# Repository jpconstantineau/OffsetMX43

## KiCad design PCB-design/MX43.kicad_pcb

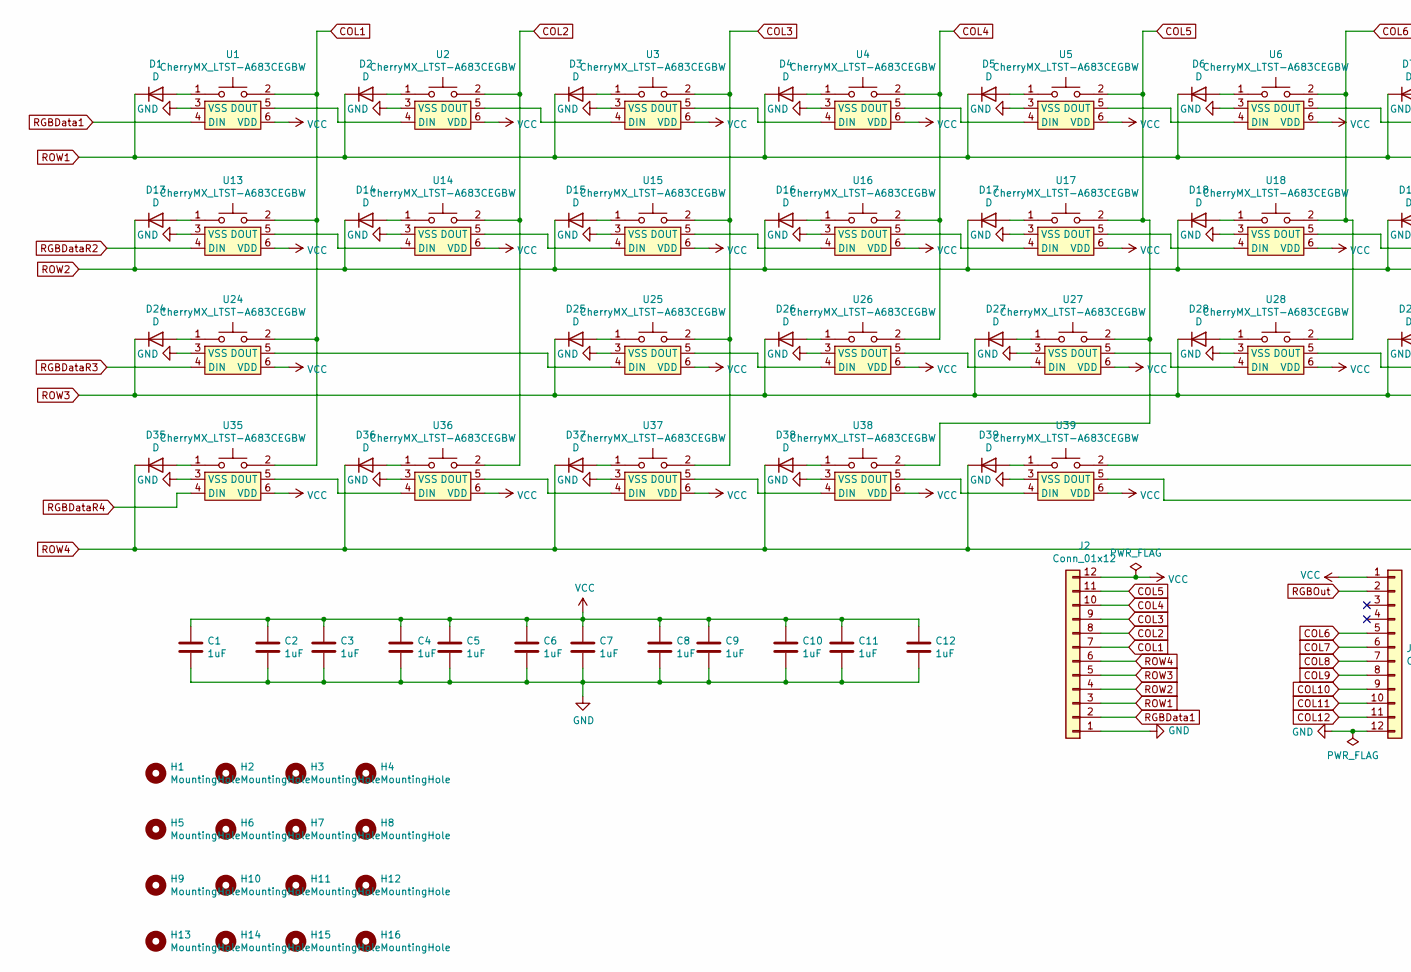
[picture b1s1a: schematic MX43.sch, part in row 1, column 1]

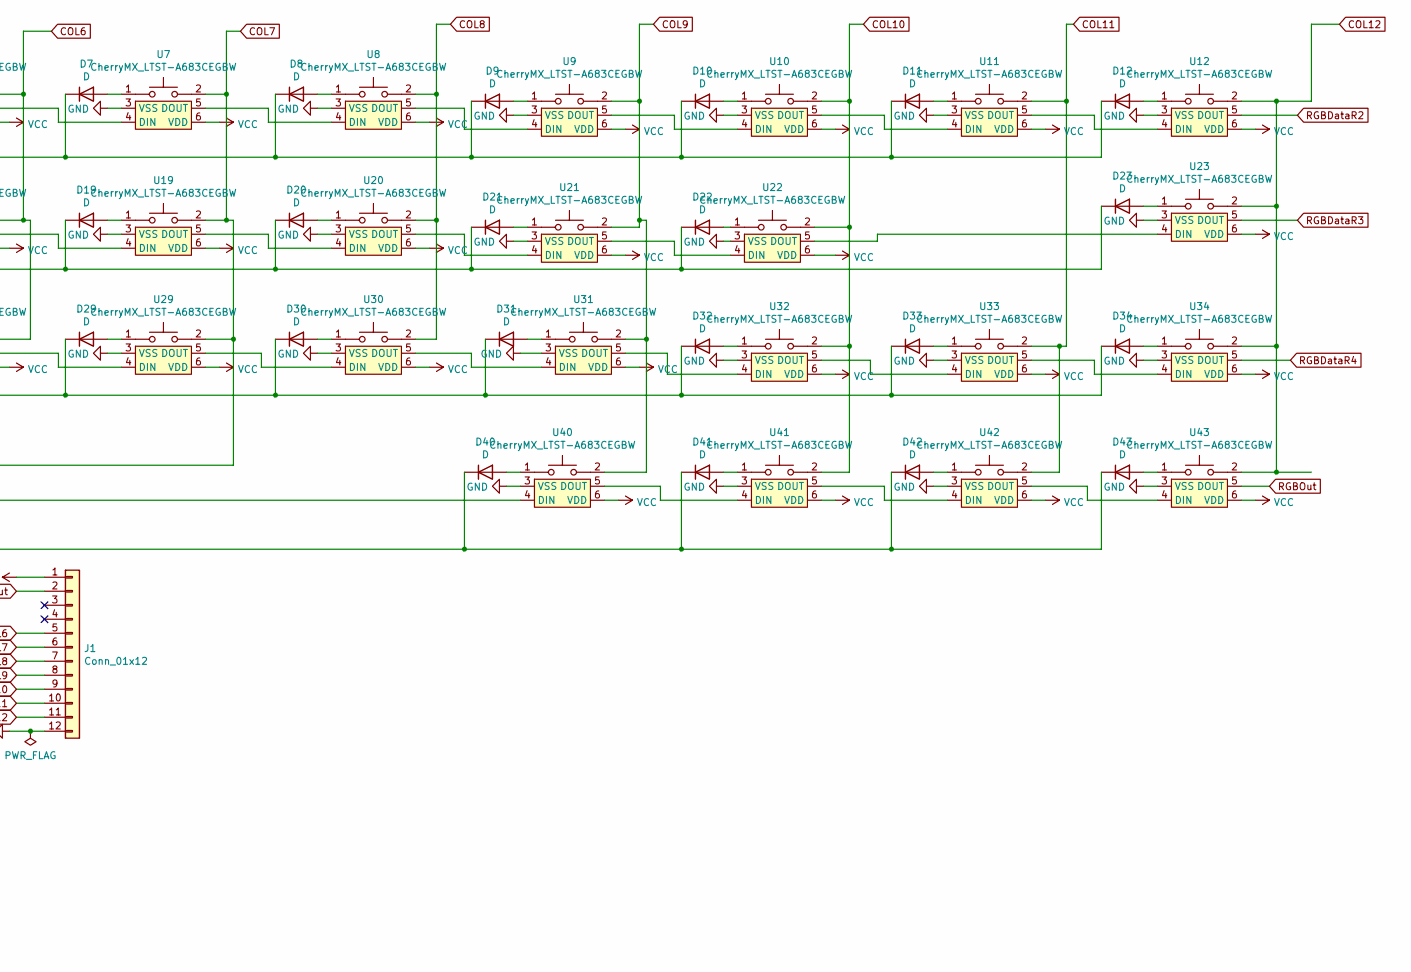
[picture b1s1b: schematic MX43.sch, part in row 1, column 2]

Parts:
C1, C2, C3, C4, C5, C6, C7, C8, C9, C10, C11, C12: 1uF; C_0805_2012Metric
D1, D2, D3, D4, D5, D6, D7, D8, D9, D10, D11, D12, D13, D14, D15, D16, D17, D18, D19, D20, D21, D22, D23, D24, D25, D26, D27, D28, D29, D30, D31, D32, D33, D34, D35, D36, D37, D38, D39, D40, D41, D42, D43: D; D_SOD-123
H1, H2, H3, H4, H5, H6, H7, H8, H9, H10, H11, H12, H13, H14, H15, H16: MountingHole; MountingHole_2.2mm_M2
J1, J2: Conn_01x12; JUSHUO-AFC07-S12FCC-00_C11051_1x12-1MP_P0.50mm_Horizontal
U1, U2, U3, U4, U5, U6, U7, U8, U9, U10, U11, U12, U14, U15, U16, U17, U18, U19, U20, U21, U22, U25, U26, U27, U28, U29, U30, U31, U32, U33, U34, U35, U36, U37, U40, U41, U42, U43: CherryMX_LTST-A683CEGBW; CherryMX_1.00u_PCB_KailhSocket_LTST-A683CEGBW-Rotated
U13: CherryMX_LTST-A683CEGBW; CherryMX_1.25u_PCB_KailhSocket_LTST-A683CEGBW-Rotated
U23: CherryMX_LTST-A683CEGBW; CherryMX_1.75u_PCB_KailhSocket_LTST-A683CEGBW-Rotated
U24: CherryMX_LTST-A683CEGBW; CherryMX_2.00u_PCB_KailhSocket_StabWireBottom_LTST-A683CEGB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
U38: CherryMX_LTST-A683CEGBW; CherryMX_2.75u_PCB_KailhSocket_StabWireBottom_LTST-A683CEGB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
U39: CherryMX_LTST-A683CEGBW; CherryMX_2.25u_PCB_KailhSocket_StabWireBottom_LTST-A683CEGB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

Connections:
COL1: J2.7, U1.2, U13.2, U24.2, U35.2
COL2: J2.8, U2.2, U14.2, U36.2
COL3: J2.9, U3.2, U15.2, U25.2, U37.2
COL4: J2.10, U4.2, U16.2, U26.2
COL5: J2.11, U5.2, U17.2, U27.2, U38.2
COL6: J1.5, U6.2, U18.2, U28.2
COL7: J1.6, U7.2, U19.2, U29.2, U39.2
COL8: J1.7, U8.2, U20.2, U30.2
COL9: J1.8, U9.2, U21.2, U31.2, U40.2
COL10: J1.9, U10.2, U22.2, U32.2, U41.2
COL11: J1.10, U11.2, U33.2, U42.2
COL12: J1.11, U12.2, U23.2, U34.2, U43.2
GND: C1.2, C2.2, C3.2, C4.2, C5.2, C6.2, C7.2, C8.2, C9.2, C10.2, C11.2, C12.2, J1.12, J2.1, U1.3 (VSS), U2.3 (VSS), U3.3 (VSS), U4.3 (VSS), U5.3 (VSS), U6.3 (VSS), U7.3 (VSS), U8.3 (VSS), U9.3 (VSS), U10.3 (VSS), U11.3 (VSS), U12.3 (VSS), U13.3 (VSS), U14.3 (VSS), U15.3 (VSS), U16.3 (VSS), U17.3 (VSS), U18.3 (VSS), U19.3 (VSS), U20.3 (VSS), U21.3 (VSS), U22.3 (VSS), U23.3 (VSS), U24.3 (VSS), U25.3 (VSS), U26.3 (VSS), U27.3 (VSS), U28.3 (VSS), U29.3 (VSS), U30.3 (VSS), U31.3 (VSS), U32.3 (VSS), U33.3 (VSS), U34.3 (VSS), U35.3 (VSS), U36.3 (VSS), U37.3 (VSS), U38.3 (VSS), U39.3 (VSS), U40.3 (VSS), U41.3 (VSS), U42.3 (VSS), U43.3 (VSS)
unnamed: D1.2 (A), U1.1
unnamed: D2.2 (A), U2.1
unnamed: D3.2 (A), U3.1
unnamed: D4.2 (A), U4.1
unnamed: D5.2 (A), U5.1
unnamed: D6.2 (A), U6.1
unnamed: D7.2 (A), U7.1
unnamed: D8.2 (A), U8.1
unnamed: D9.2 (A), U9.1
unnamed: D10.2 (A), U10.1
unnamed: D11.2 (A), U11.1
unnamed: D12.2 (A), U12.1
unnamed: D13.2 (A), U13.1
unnamed: D14.2 (A), U14.1
unnamed: D15.2 (A), U15.1
unnamed: D16.2 (A), U16.1
unnamed: D17.2 (A), U17.1
unnamed: D18.2 (A), U18.1
unnamed: D19.2 (A), U19.1
unnamed: D20.2 (A), U20.1
unnamed: D21.2 (A), U21.1
unnamed: D22.2 (A), U22.1
unnamed: D23.2 (A), U23.1
unnamed: D24.2 (A), U24.1
unnamed: D25.2 (A), U25.1
unnamed: D26.2 (A), U26.1
unnamed: D27.2 (A), U27.1
unnamed: D28.2 (A), U28.1
unnamed: D29.2 (A), U29.1
unnamed: D30.2 (A), U30.1
unnamed: D31.2 (A), U31.1
unnamed: D32.2 (A), U32.1
unnamed: D33.2 (A), U33.1
unnamed: D34.2 (A), U34.1
unnamed: D35.2 (A), U35.1
unnamed: D36.2 (A), U36.1
unnamed: D37.2 (A), U37.1
unnamed: D38.2 (A), U38.1
unnamed: D39.2 (A), U39.1
unnamed: D40.2 (A), U40.1
unnamed: D41.2 (A), U41.1
unnamed: D42.2 (A), U42.1
unnamed: D43.2 (A), U43.1
unnamed: U1.5 (DOUT), U2.4 (DIN)
unnamed: U2.5 (DOUT), U3.4 (DIN)
unnamed: U3.5 (DOUT), U4.4 (DIN)
unnamed: U4.5 (DOUT), U5.4 (DIN)
unnamed: U5.5 (DOUT), U6.4 (DIN)
unnamed: U6.5 (DOUT), U7.4 (DIN)
unnamed: U7.5 (DOUT), U8.4 (DIN)
unnamed: U8.5 (DOUT), U9.4 (DIN)
unnamed: U9.5 (DOUT), U10.4 (DIN)
unnamed: U10.5 (DOUT), U11.4 (DIN)
unnamed: U11.5 (DOUT), U12.4 (DIN)
unnamed: U13.5 (DOUT), U14.4 (DIN)
unnamed: U14.5 (DOUT), U15.4 (DIN)
unnamed: U15.5 (DOUT), U16.4 (DIN)
unnamed: U16.5 (DOUT), U17.4 (DIN)
unnamed: U17.5 (DOUT), U18.4 (DIN)
unnamed: U18.5 (DOUT), U19.4 (DIN)
unnamed: U19.5 (DOUT), U20.4 (DIN)
unnamed: U20.5 (DOUT), U21.4 (DIN)
unnamed: U21.5 (DOUT), U22.4 (DIN)
unnamed: U22.5 (DOUT), U23.4 (DIN)
unnamed: U24.5 (DOUT), U25.4 (DIN)
unnamed: U25.5 (DOUT), U26.4 (DIN)
unnamed: U26.5 (DOUT), U27.4 (DIN)
unnamed: U27.5 (DOUT), U28.4 (DIN)
unnamed: U28.5 (DOUT), U29.4 (DIN)
unnamed: U29.5 (DOUT), U30.4 (DIN)
unnamed: U30.5 (DOUT), U31.4 (DIN)
unnamed: U31.5 (DOUT), U32.4 (DIN)
unnamed: U32.5 (DOUT), U33.4 (DIN)
unnamed: U33.5 (DOUT), U34.4 (DIN)
unnamed: U35.5 (DOUT), U36.4 (DIN)
unnamed: U36.5 (DOUT), U37.4 (DIN)
unnamed: U37.5 (DOUT), U38.4 (DIN)
unnamed: U38.5 (DOUT), U39.4 (DIN)
unnamed: U39.5 (DOUT), U40.4 (DIN)
unnamed: U40.5 (DOUT), U41.4 (DIN)
unnamed: U41.5 (DOUT), U42.4 (DIN)
unnamed: U42.5 (DOUT), U43.4 (DIN)
RGBData1: J2.2, U1.4 (DIN)
RGBDataR2: U12.5 (DOUT), U13.4 (DIN)
RGBDataR3: U23.5 (DOUT), U24.4 (DIN)
RGBDataR4: U34.5 (DOUT), U35.4 (DIN)
RGBOut: J1.2, U43.5 (DOUT)
ROW1: D1.1 (K), D2.1 (K), D3.1 (K), D4.1 (K), D5.1 (K), D6.1 (K), D7.1 (K), D8.1 (K), D9.1 (K), D10.1 (K), D11.1 (K), D12.1 (K), J2.3
ROW2: D13.1 (K), D14.1 (K), D15.1 (K), D16.1 (K), D17.1 (K), D18.1 (K), D19.1 (K), D20.1 (K), D21.1 (K), D22.1 (K), D23.1 (K), J2.4
ROW3: D24.1 (K), D25.1 (K), D26.1 (K), D27.1 (K), D28.1 (K), D29.1 (K), D30.1 (K), D31.1 (K), D32.1 (K), D33.1 (K), D34.1 (K), J2.5
ROW4: D35.1 (K), D36.1 (K), D37.1 (K), D38.1 (K), D39.1 (K), D40.1 (K), D41.1 (K), D42.1 (K), D43.1 (K), J2.6
VCC: C1.1, C2.1, C3.1, C4.1, C5.1, C6.1, C7.1, C8.1, C9.1, C10.1, C11.1, C12.1, J1.1, J2.12, U1.6 (VDD), U2.6 (VDD), U3.6 (VDD), U4.6 (VDD), U5.6 (VDD), U6.6 (VDD), U7.6 (VDD), U8.6 (VDD), U9.6 (VDD), U10.6 (VDD), U11.6 (VDD), U12.6 (VDD), U13.6 (VDD), U14.6 (VDD), U15.6 (VDD), U16.6 (VDD), U17.6 (VDD), U18.6 (VDD), U19.6 (VDD), U20.6 (VDD), U21.6 (VDD), U22.6 (VDD), U23.6 (VDD), U24.6 (VDD), U25.6 (VDD), U26.6 (VDD), U27.6 (VDD), U28.6 (VDD), U29.6 (VDD), U30.6 (VDD), U31.6 (VDD), U32.6 (VDD), U33.6 (VDD), U34.6 (VDD), U35.6 (VDD), U36.6 (VDD), U37.6 (VDD), U38.6 (VDD), U39.6 (VDD), U40.6 (VDD), U41.6 (VDD), U42.6 (VDD), U43.6 (VDD)

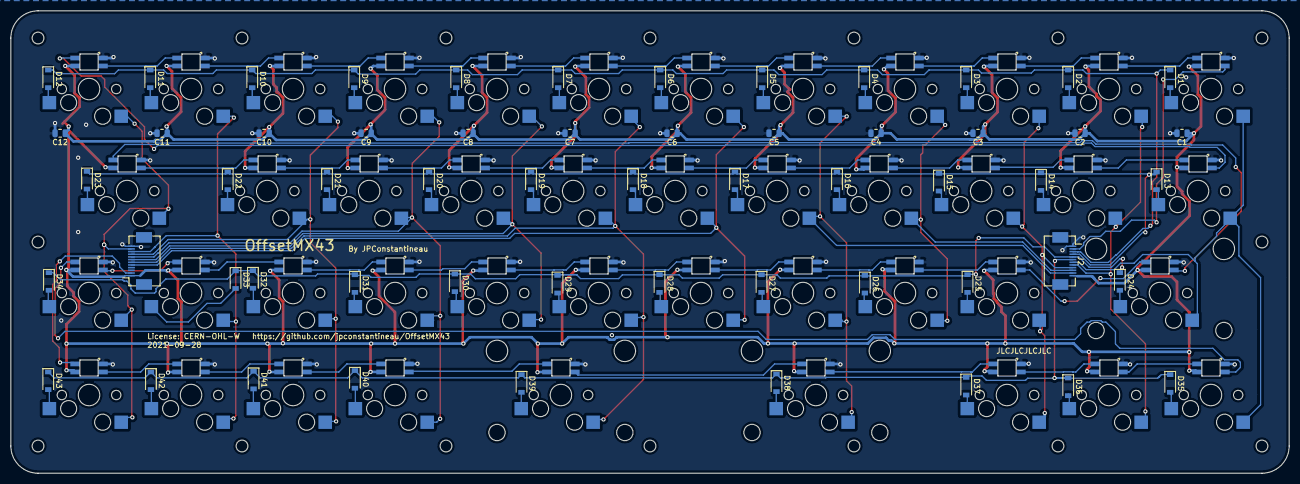
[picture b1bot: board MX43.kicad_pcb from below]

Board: 2 copper layers, 238.8 x 86.4 mm, 116 parts (57 on the bottom side), 105 nets.

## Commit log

2021-09-20 initial design
2021-10-04 minor updates

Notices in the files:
PCB-design/MX43.kicad_pcb:
License: CERN-OHL-W https://github.com/jpconstantineau/OffsetMX43
